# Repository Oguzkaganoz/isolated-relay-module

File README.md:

# Isolated Relay Module

This project is a compact and reliable relay module designed to control high-voltage loads using a microcontroller (e.g., Arduino, ESP32). It features optical isolation to ensure the safety of your controller by separating the low-voltage control logic from high-voltage circuits.

## Features
- **Optical Isolation:** Prevents electrical noise and high-voltage spikes from damaging your microcontroller.
- **Compact PCB Design:** Optimized for space-constrained industrial or hobbyist applications.
- **Professional Documentation:** Includes an Interactive BOM for easy assembly.

## Project Contents
- `gucmodulu.kicad_pcb`: PCB layout file.
- `gucmodulu.kicad_sch`: Schematic design.
- `ibom.html`: Interactive Bill of Materials for assembly (open this in your browser).
- `gucmodulu.step`: 3D model of the module for mechanical integration.

## How to View
1. **To inspect the design:** You can open the project files using [KiCad](https://www.kicad.org/).
2. **For assembly:** Open the `ibom.html` file in your web browser. It provides a visual guide and a searchable list of components.
3. **3D Model:** You can view the module in 3D directly within the GitHub interface by opening the `gucmodulu.step` file.

## License
This project is open-source. Feel free to use, modify, and improve it!

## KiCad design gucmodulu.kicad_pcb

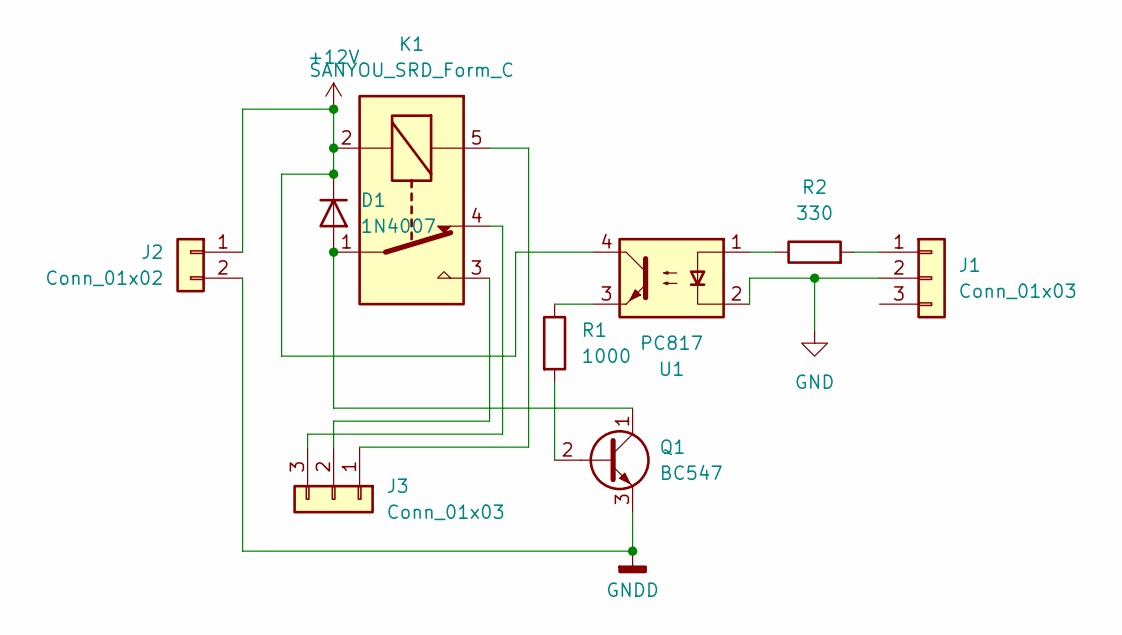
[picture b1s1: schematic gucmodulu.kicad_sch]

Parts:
D1: 1N4007; D_DO-41_SOD81_P7.62mm_Horizontal
J1, J3: Conn_01x03; TerminalBlock_Phoenix_MKDS-1,5-3_1x03_P5.00mm_Horizontal
J2: Conn_01x02; TerminalBlock_Phoenix_MKDS-1,5-2_1x02_P5.00mm_Horizontal
K1: SANYOU_SRD_Form_C; Relay_SPDT_SANYOU_SRD_Series_Form_C
Q1: BC547; TO-92_Inline
R1: 1000; R_Axial_DIN0207_L6.3mm_D2.5mm_P7.62mm_Horizontal
R2: 330; R_Axial_DIN0207_L6.3mm_D2.5mm_P7.62mm_Horizontal
U1: PC817; DIP-4_W7.62mm

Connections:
+12V: D1.1 (K), J2.1, K1.2, U1.4
GND: J1.2, U1.2
GNDD: J2.2, Q1.3 (E)
unnamed: D1.2 (A), K1.1, Q1.1 (C)
unnamed: J1.1, R2.2
unnamed: J3.1, K1.5
unnamed: J3.2, K1.3
unnamed: J3.3, K1.4
unnamed: Q1.2 (B), R1.2
unnamed: R1.1, U1.3
unnamed: R2.1, U1.1

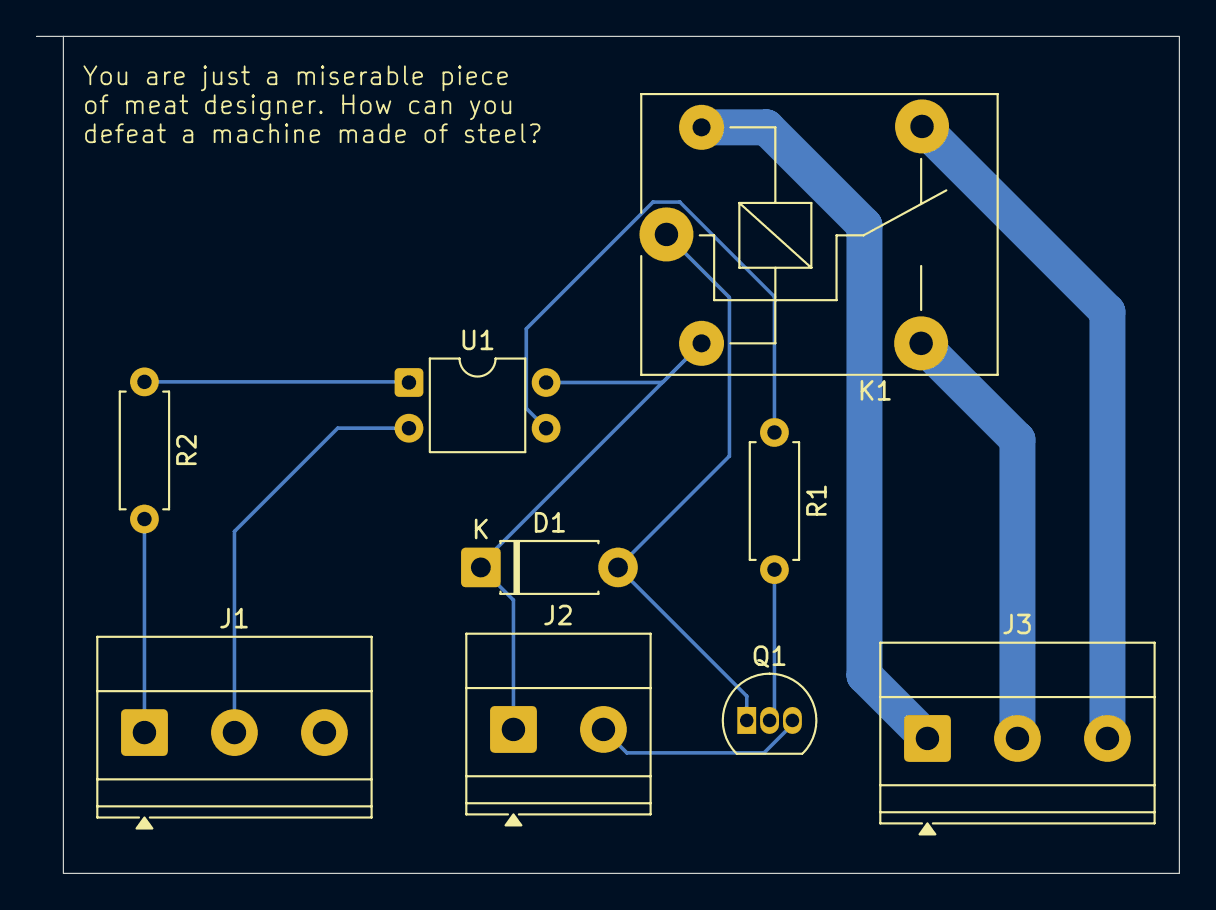
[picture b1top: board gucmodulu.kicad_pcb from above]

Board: 2 copper layers, 63.5 x 46.5 mm, 9 parts (0 on the bottom side), 11 nets.

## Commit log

2026-06-12 First commit: Isolated Relay Card design is completed
2026-06-12 Klasör temizlendi, projeye sadece gerekli dosyalar bırakıldı
2026-06-12 BOM dosyası eklendi, proje dokümantasyonu tamamlandı
2026-06-12 Add README for Isolated Relay Module
    Added project details for the Isolated Relay Module, including features, contents, and usage instructions.
2026-06-12 3D STEP model of the project is added
2026-06-12 Optimized PCB board size and finalized layout
2026-06-12 Final PCB layout: Optimized size, fixed Edge.Cuts, added files
